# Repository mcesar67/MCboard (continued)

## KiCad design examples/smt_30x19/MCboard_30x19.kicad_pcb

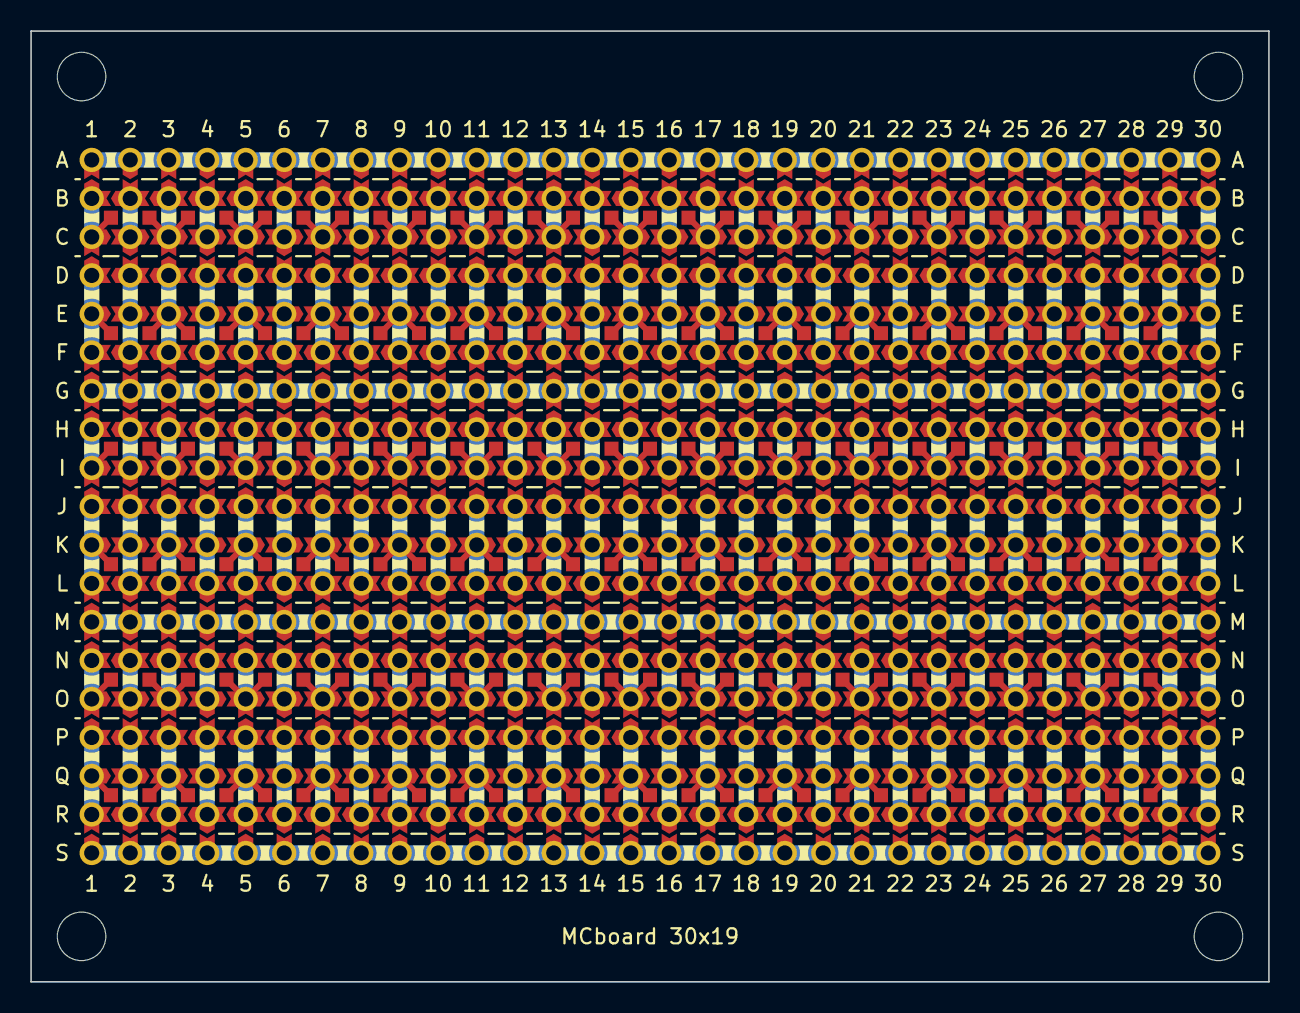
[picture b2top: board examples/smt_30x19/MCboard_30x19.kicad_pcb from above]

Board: 2 copper layers, 81.7 x 62.7 mm, 1717 parts (0 on the bottom side), 184 nets.

Parts:
PBH1, PBH2, PBH3, PBH4, PBH5, PBH6, PBH7, PBH8, PBH9, PBH10, PBH11, PBH12, PBH13, PBH14, PBH15, PBH16, PBH17, PBH18, PBH19, PBH20, PBH21, PBH22, PBH23, PBH24, PBH25, PBH26, PBH27, PBH28, PBH29, PBH30, PBH31, PBH32, PBH33, PBH34, PBH35, PBH36, PBH37, PBH38, PBH39, PBH40, PBH41, PBH42, PBH43, PBH44, PBH45, PBH46, PBH47, PBH48, PBH49, PBH50, PBH51, PBH52, PBH53, PBH54, PBH55, PBH56, PBH57, PBH58, PBH59, PBH60, PBH61, PBH62, PBH63, PBH64, PBH65, PBH66, PBH67, PBH68, PBH69, PBH70, PBH71, PBH72, PBH73, PBH74, PBH75, PBH76, PBH77, PBH78, PBH79, PBH80, PBH81, PBH82, PBH83, PBH84, PBH85, PBH86, PBH87, PBH88, PBH89, PBH90, PBH91, PBH92, PBH93, PBH94, PBH95, PBH96, PBH97, PBH98, PBH99, PBH100, PBH101, PBH102, PBH103, PBH104, PBH105, PBH106, PBH107, PBH108, PBH109, PBH110, PBH111, PBH112, PBH113, PBH114, PBH115, PBH116, PBH117, PBH118, PBH119, PBH120, PBH121, PBH122, PBH123, PBH124, PBH125, PBH126, PBH127, PBH128, PBH129, PBH130, PBH131, PBH132, PBH133, PBH134, PBH135, PBH136, PBH137, PBH138, PBH139, PBH140, PBH141, PBH142, PBH143, PBH144, PBH145, PBH146, PBH147, PBH148, PBH149, PBH150, PBH151, PBH152, PBH153, PBH154, PBH155, PBH156, PBH157, PBH158, PBH159, PBH160, PBH161, PBH162, PBH163, PBH164, PBH165, PBH166, PBH167, PBH168, PBH169, PBH170, PBH171, PBH172, PBH173, PBH174, PBH175, PBH176, PBH177, PBH178, PBH179, PBH180, PBH181, PBH182, PBH183, PBH184, PBH185, PBH186, PBH187, PBH188, PBH189, PBH190, PBH191, PBH192, PBH193, PBH194, PBH195, PBH196, PBH197, PBH198, PBH199, PBH200, PBH201, PBH202, PBH203, PBH204, PBH205, PBH206, PBH207, PBH208, PBH209, PBH210, PBH211, PBH212, PBH213, PBH214, PBH215, PBH216, PBH217, PBH218, PBH219, PBH220, PBH221, PBH222, PBH223, PBH224, PBH225, PBH226, PBH227, PBH228, PBH229, PBH230, PBH231, PBH232, PBH233, PBH234, PBH235, PBH236, PBH237, PBH238, PBH239, PBH240, PBH241, PBH242, PBH243, PBH244, PBH245, PBH246, PBH247, PBH248, PBH249, PBH250, PBH251, PBH252, PBH253, PBH254, PBH255, PBH256, PBH257, PBH258, PBH259, PBH260, PBH261, PBH262, PBH263, PBH264, PBH265, PBH266, PBH267, PBH268, PBH269, PBH270, PBH271, PBH272, PBH273, PBH274, PBH275, PBH276, PBH277, PBH278, PBH279, PBH280, PBH281, PBH282, PBH283, PBH284, PBH285, PBH286, PBH287, PBH288, PBH289, PBH290, PBH291, PBH292, PBH293, PBH294, PBH295, PBH296, PBH297, PBH298, PBH299, PBH300, PBH301, PBH302, PBH303, PBH304, PBH305, PBH306, PBH307, PBH308, PBH309, PBH310, PBH311, PBH312, PBH313, PBH314, PBH315, PBH316, PBH317, PBH318, PBH319, PBH320, PBH321, PBH322, PBH323, PBH324, PBH325, PBH326, PBH327, PBH328, PBH329, PBH330, PBH331, PBH332, PBH333, PBH334, PBH335, PBH336, PBH337, PBH338, PBH339, PBH340, PBH341, PBH342, PBH343, PBH344, PBH345, PBH346, PBH347, PBH348, PBH349, PBH350, PBH351, PBH352, PBH353, PBH354, PBH355, PBH356, PBH357, PBH358, PBH359, PBH360, PBH361, PBH362, PBH363, PBH364, PBH365, PBH366, PBH367, PBH368, PBH369, PBH370, PBH371, PBH372, PBH373, PBH374, PBH375, PBH376, PBH377, PBH378, PBH379, PBH380, PBH381, PBH382, PBH383, PBH384, PBH385, PBH386, PBH387, PBH388, PBH389, PBH390, PBH391, PBH392, PBH393, PBH394, PBH395, PBH396, PBH397, PBH398, PBH399, PBH400, PBH401, PBH402, PBH403, PBH404, PBH405, PBH406, PBH407, PBH408, PBH409, PBH410, PBH411, PBH412, PBH413, PBH414, PBH415, PBH416, PBH417, PBH418, PBH419, PBH420, PBH421, PBH422, PBH423, PBH424, PBH425, PBH426, PBH427, PBH428, PBH429, PBH430, PBH431, PBH432, PBH433, PBH434, PBH435, PBH436, PBH437, PBH438, PBH439, PBH440, PBH441, PBH442, PBH443, PBH444, PBH445, PBH446, PBH447, PBH448, PBH449, PBH450, PBH451, PBH452, PBH453, PBH454, PBH455, PBH456, PBH457, PBH458, PBH459, PBH460, PBH461, PBH462, PBH463, PBH464, PBH465, PBH466, PBH467, PBH468, PBH469, PBH470, PBH471, PBH472, PBH473, PBH474, PBH475, PBH476, PBH477, PBH478, PBH479, PBH480, PBH481, PBH482, PBH483, PBH484, PBH485, PBH486, PBH487, PBH488, PBH489, PBH490, PBH491, PBH492, PBH493, PBH494, PBH495, PBH496, PBH497, PBH498, PBH499, PBH500, PBH501, PBH502, PBH503, PBH504, PBH505, PBH506, PBH507, PBH508, PBH509, PBH510, PBH511, PBH512, PBH513, PBH514, PBH515, PBH516, PBH517, PBH518, PBH519, PBH520, PBH521, PBH522, PBH523, PBH524, PBH525, PBH526, PBH527, PBH528, PBH529, PBH530, PBH531, PBH532, PBH533, PBH534, PBH535, PBH536, PBH537, PBH538, PBH539, PBH540, PBH541, PBH542, PBH543, PBH544, PBH545, PBH546, PBH547, PBH548, PBH549, PBH550, PBH551, PBH552, PBH553, PBH554, PBH555, PBH556, PBH557, PBH558, PBH559, PBH560, PBH561, PBH562, PBH563, PBH564, PBH565, PBH566, PBH567, PBH568, PBH569, PBH570: hole; Hole
PBIS1, PBIS2, PBIS3, PBIS4, PBIS5, PBIS6, PBIS7, PBIS8, PBIS9, PBIS10, PBIS11, PBIS12, PBIS13, PBIS14, PBIS15, PBIS16, PBIS17, PBIS18, PBIS19, PBIS20, PBIS21, PBIS22, PBIS23, PBIS24, PBIS25, PBIS26, PBIS27, PBIS28, PBIS29, PBIS30, PBIS31, PBIS32, PBIS33, PBIS34, PBIS35, PBIS36, PBIS37, PBIS38, PBIS39, PBIS40, PBIS41, PBIS42, PBIS43, PBIS44, PBIS45, PBIS46, PBIS47, PBIS48, PBIS49, PBIS50, PBIS51, PBIS52, PBIS53, PBIS54, PBIS55, PBIS56, PBIS57, PBIS58, PBIS59, PBIS60, PBIS61, PBIS62, PBIS63, PBIS64, PBIS65, PBIS66, PBIS67, PBIS68, PBIS69, PBIS70, PBIS71, PBIS72, PBIS73, PBIS74, PBIS75, PBIS76, PBIS77, PBIS78, PBIS79, PBIS80, PBIS81, PBIS82, PBIS83, PBIS84, PBIS85, PBIS86, PBIS87, PBIS88, PBIS89, PBIS90, PBIS91, PBIS92, PBIS93, PBIS94, PBIS95, PBIS96, PBIS97, PBIS98, PBIS99, PBIS100, PBIS101, PBIS102, PBIS103, PBIS104, PBIS105, PBIS106, PBIS107, PBIS108, PBIS109, PBIS110, PBIS111, PBIS112, PBIS113, PBIS114, PBIS115, PBIS116, PBIS117, PBIS118, PBIS119, PBIS120, PBIS121, PBIS122, PBIS123, PBIS124, PBIS125, PBIS126, PBIS127, PBIS128, PBIS129, PBIS130, PBIS131, PBIS132, PBIS133, PBIS134, PBIS135, PBIS136, PBIS137, PBIS138, PBIS139, PBIS140, PBIS141, PBIS142, PBIS143, PBIS144, PBIS145, PBIS146, PBIS147, PBIS148, PBIS149, PBIS150, PBIS151, PBIS152, PBIS153, PBIS154, PBIS155, PBIS156, PBIS157, PBIS158, PBIS159, PBIS160, PBIS161, PBIS162, PBIS163, PBIS164, PBIS165, PBIS166, PBIS167, PBIS168: island; Island
PBJP1, PBJP2, PBJP3, PBJP4, PBJP5, PBJP6, PBJP7, PBJP8, PBJP9, PBJP10, PBJP11, PBJP12, PBJP13, PBJP14, PBJP15, PBJP16, PBJP17, PBJP18, PBJP19, PBJP20, PBJP21, PBJP22, PBJP23, PBJP24, PBJP25, PBJP26, PBJP27, PBJP28, PBJP29, PBJP30, PBJP31, PBJP32, PBJP33, PBJP34, PBJP35, PBJP36, PBJP37, PBJP38, PBJP39, PBJP40, PBJP41, PBJP42, PBJP43, PBJP44, PBJP45, PBJP46, PBJP47, PBJP48, PBJP49, PBJP50, PBJP51, PBJP52, PBJP53, PBJP54, PBJP55, PBJP56, PBJP57, PBJP58, PBJP59, PBJP60, PBJP61, PBJP62, PBJP63, PBJP64, PBJP65, PBJP66, PBJP67, PBJP68, PBJP69, PBJP70, PBJP71, PBJP72, PBJP73, PBJP74, PBJP75, PBJP76, PBJP77, PBJP78, PBJP79, PBJP80, PBJP81, PBJP82, PBJP83, PBJP84, PBJP85, PBJP86, PBJP87, PBJP88, PBJP89, PBJP90, PBJP91, PBJP92, PBJP93, PBJP94, PBJP95, PBJP96, PBJP97, PBJP98, PBJP99, PBJP100, PBJP101, PBJP102, PBJP103, PBJP104, PBJP105, PBJP106, PBJP107, PBJP108, PBJP109, PBJP110, PBJP111, PBJP112, PBJP113, PBJP114, PBJP115, PBJP116, PBJP117, PBJP118, PBJP119, PBJP120, PBJP121, PBJP122, PBJP123, PBJP124, PBJP125, PBJP126, PBJP127, PBJP128, PBJP129, PBJP130, PBJP131, PBJP132, PBJP133, PBJP134, PBJP135, PBJP136, PBJP137, PBJP138, PBJP139, PBJP140, PBJP141, PBJP142, PBJP143, PBJP144, PBJP145, PBJP146, PBJP147, PBJP148, PBJP149, PBJP150, PBJP151, PBJP152, PBJP153, PBJP154, PBJP155, PBJP156, PBJP157, PBJP158, PBJP159, PBJP160, PBJP161, PBJP162, PBJP163, PBJP164, PBJP165, PBJP166, PBJP167, PBJP168, PBJP169, PBJP170, PBJP171, PBJP172, PBJP173, PBJP174, PBJP175, PBJP176, PBJP177, PBJP178, PBJP179, PBJP180, PBJP181, PBJP182, PBJP183, PBJP184, PBJP185, PBJP186, PBJP187, PBJP188, PBJP189, PBJP190, PBJP191, PBJP192, PBJP193, PBJP194, PBJP195, PBJP196, PBJP197, PBJP198, PBJP199, PBJP200, PBJP201, PBJP202, PBJP203, PBJP204, PBJP205, PBJP206, PBJP207, PBJP208, PBJP209, PBJP210, PBJP211, PBJP212, PBJP213, PBJP214, PBJP215, PBJP216, PBJP217, PBJP218, PBJP219, PBJP220, PBJP221, PBJP222, PBJP223, PBJP224, PBJP225, PBJP226, PBJP227, PBJP228, PBJP229, PBJP230, PBJP231, PBJP232, PBJP233, PBJP234, PBJP235, PBJP236, PBJP237, PBJP238, PBJP239, PBJP240, PBJP241, PBJP242, PBJP243, PBJP244, PBJP245, PBJP246, PBJP247, PBJP248, PBJP249, PBJP250, PBJP251, PBJP252, PBJP253, PBJP254, PBJP255, PBJP256, PBJP257, PBJP258, PBJP259, PBJP260, PBJP261, PBJP262, PBJP263, PBJP264, PBJP265, PBJP266, PBJP267, PBJP268, PBJP269, PBJP270: chevron; ChevronJumper
PBJT1, PBJT2, PBJT3, PBJT4, PBJT5, PBJT6, PBJT7, PBJT8, PBJT9, PBJT10, PBJT11, PBJT12, PBJT13, PBJT14, PBJT15, PBJT16, PBJT17, PBJT18, PBJT19, PBJT20, PBJT21, PBJT22, PBJT23, PBJT24, PBJT25, PBJT26, PBJT27, PBJT28, PBJT29, PBJT30, PBJT31, PBJT32, PBJT33, PBJT34, PBJT35, PBJT36, PBJT37, PBJT38, PBJT39, PBJT40, PBJT41, PBJT42, PBJT43, PBJT44, PBJT45, PBJT46, PBJT47, PBJT48, PBJT49, PBJT50, PBJT51, PBJT52, PBJT53, PBJT54, PBJT55, PBJT56, PBJT57, PBJT58, PBJT59, PBJT60, PBJT61, PBJT62, PBJT63, PBJT64, PBJT65, PBJT66, PBJT67, PBJT68, PBJT69, PBJT70, PBJT71, PBJT72, PBJT73, PBJT74, PBJT75, PBJT76, PBJT77, PBJT78, PBJT79, PBJT80, PBJT81, PBJT82, PBJT83, PBJT84, PBJT85, PBJT86, PBJT87, PBJT88, PBJT89, PBJT90, PBJT91, PBJT92, PBJT93, PBJT94, PBJT95, PBJT96, PBJT97, PBJT98, PBJT99, PBJT100, PBJT101, PBJT102, PBJT103, PBJT104, PBJT105, PBJT106, PBJT107, PBJT108, PBJT109, PBJT110, PBJT111, PBJT112, PBJT113, PBJT114, PBJT115, PBJT116, PBJT117, PBJT118, PBJT119, PBJT120, PBJT121, PBJT122, PBJT123, PBJT124, PBJT125, PBJT126, PBJT127, PBJT128, PBJT129, PBJT130, PBJT131, PBJT132, PBJT133, PBJT134, PBJT135, PBJT136, PBJT137, PBJT138, PBJT139, PBJT140, PBJT141, PBJT142, PBJT143, PBJT144, PBJT145, PBJT146, PBJT147, PBJT148, PBJT149, PBJT150, PBJT151, PBJT152, PBJT153, PBJT154, PBJT155, PBJT156, PBJT157, PBJT158, PBJT159, PBJT160, PBJT161, PBJT162, PBJT163, PBJT164, PBJT165, PBJT166, PBJT167, PBJT168, PBJT169, PBJT170, PBJT171, PBJT172, PBJT173, PBJT174, PBJT175, PBJT176, PBJT177, PBJT178, PBJT179, PBJT180, PBJT181, PBJT182, PBJT183, PBJT184, PBJT185, PBJT186, PBJT187, PBJT188, PBJT189, PBJT190, PBJT191, PBJT192, PBJT193, PBJT194, PBJT195, PBJT196, PBJT197, PBJT198, PBJT199, PBJT200, PBJT201, PBJT202, PBJT203, PBJT204, PBJT205, PBJT206, PBJT207, PBJT208, PBJT209, PBJT210, PBJT211, PBJT212, PBJT213, PBJT214, PBJT215, PBJT216, PBJT217, PBJT218, PBJT219, PBJT220, PBJT221, PBJT222, PBJT223, PBJT224, PBJT225, PBJT226, PBJT227, PBJT228, PBJT229, PBJT230, PBJT231, PBJT232, PBJT233, PBJT234, PBJT235, PBJT236, PBJT237, PBJT238, PBJT239, PBJT240, PBJT241, PBJT242, PBJT243, PBJT244, PBJT245, PBJT246, PBJT247, PBJT248, PBJT249, PBJT250, PBJT251, PBJT252, PBJT253, PBJT254, PBJT255, PBJT256, PBJT257, PBJT258, PBJT259, PBJT260, PBJT261, PBJT262, PBJT263, PBJT264, PBJT265, PBJT266, PBJT267, PBJT268, PBJT269, PBJT270, PBJT271, PBJT272, PBJT273, PBJT274, PBJT275, PBJT276, PBJT277, PBJT278, PBJT279, PBJT280, PBJT281, PBJT282, PBJT283, PBJT284, PBJT285, PBJT286, PBJT287, PBJT288, PBJT289, PBJT290, PBJT291, PBJT292, PBJT293, PBJT294, PBJT295, PBJT296, PBJT297, PBJT298, PBJT299, PBJT300, PBJT301, PBJT302, PBJT303, PBJT304, PBJT305, PBJT306, PBJT307, PBJT308, PBJT309, PBJT310, PBJT311, PBJT312, PBJT313, PBJT314, PBJT315, PBJT316, PBJT317, PBJT318, PBJT319, PBJT320, PBJT321, PBJT322, PBJT323, PBJT324, PBJT325, PBJT326, PBJT327, PBJT328, PBJT329, PBJT330, PBJT331, PBJT332, PBJT333, PBJT334, PBJT335, PBJT336, PBJT337, PBJT338, PBJT339, PBJT340, PBJT341, PBJT342, PBJT343, PBJT344, PBJT345, PBJT346, PBJT347, PBJT348, PBJT349, PBJT350, PBJT351, PBJT352, PBJT353, PBJT354, PBJT355, PBJT356, PBJT357, PBJT358, PBJT359, PBJT360, PBJT361, PBJT362, PBJT363, PBJT364, PBJT365, PBJT366, PBJT367, PBJT368, PBJT369, PBJT370, PBJT371, PBJT372, PBJT373, PBJT374, PBJT375, PBJT376, PBJT377, PBJT378, PBJT379, PBJT380, PBJT381, PBJT382, PBJT383, PBJT384, PBJT385, PBJT386, PBJT387, PBJT388, PBJT389, PBJT390, PBJT391, PBJT392, PBJT393, PBJT394, PBJT395, PBJT396, PBJT397, PBJT398, PBJT399, PBJT400, PBJT401, PBJT402, PBJT403, PBJT404, PBJT405, PBJT406, PBJT407, PBJT408, PBJT409, PBJT410, PBJT411, PBJT412, PBJT413, PBJT414, PBJT415, PBJT416, PBJT417, PBJT418, PBJT419, PBJT420, PBJT421, PBJT422, PBJT423, PBJT424, PBJT425, PBJT426, PBJT427, PBJT428, PBJT429, PBJT430, PBJT431, PBJT432, PBJT433, PBJT434, PBJT435, PBJT436, PBJT437, PBJT438, PBJT439, PBJT440, PBJT441, PBJT442, PBJT443, PBJT444, PBJT445, PBJT446, PBJT447, PBJT448, PBJT449, PBJT450, PBJT451, PBJT452, PBJT453, PBJT454, PBJT455, PBJT456, PBJT457, PBJT458, PBJT459, PBJT460, PBJT461, PBJT462, PBJT463, PBJT464, PBJT465, PBJT466, PBJT467, PBJT468, PBJT469, PBJT470, PBJT471, PBJT472, PBJT473, PBJT474, PBJT475, PBJT476, PBJT477, PBJT478, PBJT479, PBJT480, PBJT481, PBJT482, PBJT483, PBJT484, PBJT485, PBJT486, PBJT487, PBJT488, PBJT489, PBJT490, PBJT491, PBJT492, PBJT493, PBJT494, PBJT495, PBJT496, PBJT497, PBJT498, PBJT499, PBJT500, PBJT501, PBJT502, PBJT503, PBJT504, PBJT505, PBJT506, PBJT507, PBJT508, PBJT509, PBJT510, PBJT511, PBJT512, PBJT513, PBJT514, PBJT515, PBJT516, PBJT517, PBJT518, PBJT519, PBJT520, PBJT521, PBJT522, PBJT523, PBJT524, PBJT525, PBJT526, PBJT527, PBJT528, PBJT529, PBJT530, PBJT531, PBJT532, PBJT533, PBJT534, PBJT535, PBJT536, PBJT537, PBJT538, PBJT539, PBJT540, PBJT541, PBJT542, PBJT543, PBJT544, PBJT545, PBJT546, PBJT547, PBJT548, PBJT549, PBJT550, PBJT551, PBJT552, PBJT553, PBJT554, PBJT555, PBJT556, PBJT557, PBJT558, PBJT559, PBJT560, PBJT561, PBJT562, PBJT563, PBJT564, PBJT565, PBJT566, PBJT567, PBJT568, PBJT569, PBJT570, PBJT571, PBJT572, PBJT573, PBJT574, PBJT575, PBJT576, PBJT577, PBJT578, PBJT579, PBJT580, PBJT581, PBJT582, PBJT583, PBJT584, PBJT585, PBJT586, PBJT587, PBJT588, PBJT589, PBJT590, PBJT591, PBJT592, PBJT593, PBJT594, PBJT595, PBJT596, PBJT597, PBJT598, PBJT599, PBJT600, PBJT601, PBJT602, PBJT603, PBJT604, PBJT605, PBJT606, PBJT607, PBJT608, PBJT609, PBJT610, PBJT611, PBJT612, PBJT613, PBJT614, PBJT615, PBJT616, PBJT617, PBJT618, PBJT619, PBJT620, PBJT621, PBJT622, PBJT623, PBJT624, PBJT625, PBJT626, PBJT627, PBJT628, PBJT629, PBJT630, PBJT631, PBJT632, PBJT633, PBJT634, PBJT635, PBJT636, PBJT637, PBJT638, PBJT639, PBJT640, PBJT641, PBJT642, PBJT643, PBJT644, PBJT645, PBJT646, PBJT647, PBJT648, PBJT649, PBJT650, PBJT651, PBJT652, PBJT653, PBJT654, PBJT655, PBJT656, PBJT657, PBJT658, PBJT659, PBJT660, PBJT661, PBJT662, PBJT663, PBJT664, PBJT665, PBJT666, PBJT667, PBJT668, PBJT669, PBJT670, PBJT671, PBJT672, PBJT673, PBJT674, PBJT675, PBJT676, PBJT677, PBJT678, PBJT679, PBJT680, PBJT681, PBJT682, PBJT683, PBJT684, PBJT685, PBJT686, PBJT687, PBJT688, PBJT689, PBJT690, PBJT691, PBJT692, PBJT693, PBJT694, PBJT695, PBJT696, PBJT697, PBJT698, PBJT699, PBJT700, PBJT701, PBJT702, PBJT703, PBJT704, PBJT705: chevron; ChevronJumper
PBMH1, PBMH2, PBMH3, PBMH4: mounting hole; MountingHole

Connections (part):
BUS_R1: PBH1.1, PBH20.1, PBH39.1, PBH58.1, PBH77.1, PBH96.1, PBH115.1, PBH134.1, PBH153.1, PBH172.1, PBH191.1, PBH210.1, PBH229.1, PBH248.1, PBH267.1, PBH286.1, PBH305.1, PBH324.1, PBH343.1, PBH362.1, PBH381.1, PBH400.1, PBH419.1, PBH438.1, PBH457.1, PBH476.1, PBH495.1, PBH514.1, PBH533.1, PBH552.1, PBJP1.1, PBJP10.1, PBJP19.1, PBJP28.1, PBJP37.1, PBJP46.1, PBJP55.1, PBJP64.1, PBJP73.1, PBJP82.1, PBJP91.1, PBJP100.1, PBJP109.1, PBJP118.1, PBJP127.1, PBJP136.1, PBJP145.1, PBJP154.1, PBJP163.1, PBJP172.1, PBJP181.1, PBJP190.1, PBJP199.1, PBJP208.1, PBJP217.1, PBJP226.1, PBJP235.1, PBJP244.1, PBJP253.1, PBJP262.1, PBJT436.2, PBJT445.1, PBJT454.2, PBJT463.1, PBJT472.2, PBJT481.1, PBJT490.2, PBJT499.1, PBJT508.2, PBJT517.1, PBJT526.2, PBJT535.1, PBJT544.2, PBJT553.1, PBJT562.2, PBJT571.1, PBJT580.2, PBJT589.1, PBJT598.2, PBJT607.1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
BUS_R7: PBH7.1, PBH26.1, PBH45.1, PBH64.1, PBH83.1, PBH102.1, PBH121.1, PBH140.1, PBH159.1, PBH178.1, PBH197.1, PBH216.1, PBH235.1, PBH254.1, PBH273.1, PBH292.1, PBH311.1, PBH330.1, PBH349.1, PBH368.1, PBH387.1, PBH406.1, PBH425.1, PBH444.1, PBH463.1, PBH482.1, PBH501.1, PBH520.1, PBH539.1, PBH558.1, PBJP3.2, PBJP4.1, PBJP12.2, PBJP13.1, PBJP21.2, PBJP22.1, PBJP30.2, PBJP31.1, PBJP39.2, PBJP40.1, PBJP48.2, PBJP49.1, PBJP57.2, PBJP58.1, PBJP66.2, PBJP67.1, PBJP75.2, PBJP76.1, PBJP84.2, PBJP85.1, PBJP93.2, PBJP94.1, PBJP102.2, PBJP103.1, PBJP111.2, PBJP112.1, PBJP120.2, PBJP121.1, PBJP129.2, PBJP130.1, PBJP138.2, PBJP139.1, PBJP147.2, PBJP148.1, PBJP156.2, PBJP157.1, PBJP165.2, PBJP166.1, PBJP174.2, PBJP175.1, PBJP183.2, PBJP184.1, PBJP192.2, PBJP193.1, PBJP201.2, PBJP202.1, PBJP210.2, PBJP211.1, PBJP219.2, PBJP220.1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
BUS_R13: PBH13.1, PBH32.1, PBH51.1, PBH70.1, PBH89.1, PBH108.1, PBH127.1, PBH146.1, PBH165.1, PBH184.1, PBH203.1, PBH222.1, PBH241.1, PBH260.1, PBH279.1, PBH298.1, PBH317.1, PBH336.1, PBH355.1, PBH374.1, PBH393.1, PBH412.1, PBH431.1, PBH450.1, PBH469.1, PBH488.1, PBH507.1, PBH526.1, PBH545.1, PBH564.1, PBJP6.2, PBJP7.1, PBJP15.2, PBJP16.1, PBJP24.2, PBJP25.1, PBJP33.2, PBJP34.1, PBJP42.2, PBJP43.1, PBJP51.2, PBJP52.1, PBJP60.2, PBJP61.1, PBJP69.2, PBJP70.1, PBJP78.2, PBJP79.1, PBJP87.2, PBJP88.1, PBJP96.2, PBJP97.1, PBJP105.2, PBJP106.1, PBJP114.2, PBJP115.1, PBJP123.2, PBJP124.1, PBJP132.2, PBJP133.1, PBJP141.2, PBJP142.1, PBJP150.2, PBJP151.1, PBJP159.2, PBJP160.1, PBJP168.2, PBJP169.1, PBJP177.2, PBJP178.1, PBJP186.2, PBJP187.1, PBJP195.2, PBJP196.1, PBJP204.2, PBJP205.1, PBJP213.2, PBJP214.1, PBJP222.2, PBJP223.1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
BUS_R19: PBH19.1, PBH38.1, PBH57.1, PBH76.1, PBH95.1, PBH114.1, PBH133.1, PBH152.1, PBH171.1, PBH190.1, PBH209.1, PBH228.1, PBH247.1, PBH266.1, PBH285.1, PBH304.1, PBH323.1, PBH342.1, PBH361.1, PBH380.1, PBH399.1, PBH418.1, PBH437.1, PBH456.1, PBH475.1, PBH494.1, PBH513.1, PBH532.1, PBH551.1, PBH570.1, PBJP9.2, PBJP18.2, PBJP27.2, PBJP36.2, PBJP45.2, PBJP54.2, PBJP63.2, PBJP72.2, PBJP81.2, PBJP90.2, PBJP99.2, PBJP108.2, PBJP117.2, PBJP126.2, PBJP135.2, PBJP144.2, PBJP153.2, PBJP162.2, PBJP171.2, PBJP180.2, PBJP189.2, PBJP198.2, PBJP207.2, PBJP216.2, PBJP225.2, PBJP234.2, PBJP243.2, PBJP252.2, PBJP261.2, PBJP270.2, PBJT444.1, PBJT453.2, PBJT462.1, PBJT471.2, PBJT480.1, PBJT489.2, PBJT498.1, PBJT507.2, PBJT516.1, PBJT525.2, PBJT534.1, PBJT543.2, PBJT552.1, PBJT561.2, PBJT570.1, PBJT579.2, PBJT588.1, PBJT597.2, PBJT606.1, PBJT615.2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
C1_R2: PBH2.1, PBH3.1, PBIS1.1, PBJP1.2, PBJP2.1, PBJT1.2, PBJT30.1, PBJT436.1, PBJT437.2
C1_R4: PBH4.1, PBH5.1, PBH6.1, PBIS29.1, PBJP2.2, PBJP3.1, PBJT59.2, PBJT88.1, PBJT117.2, PBJT437.1, PBJT438.2
C1_R8: PBH8.1, PBH9.1, PBIS57.1, PBJP4.2, PBJP5.1, PBJT146.2, PBJT175.1, PBJT439.1, PBJT440.2
C1_R10: PBH10.1, PBH11.1, PBH12.1, PBIS85.1, PBJP5.2, PBJP6.1, PBJT204.2, PBJT233.1, PBJT262.2, PBJT440.1, PBJT441.2
C1_R14: PBH14.1, PBH15.1, PBIS113.1, PBJP7.2, PBJP8.1, PBJT291.2, PBJT320.1, PBJT442.1, PBJT443.2
C1_R16: PBH16.1, PBH17.1, PBH18.1, PBIS141.1, PBJP8.2, PBJP9.1, PBJT349.2, PBJT378.1, PBJT407.2, PBJT443.1, PBJT444.2
C2_R2: PBH21.1, PBH22.1, PBJP10.2, PBJP11.1, PBJT1.1, PBJT2.2, PBJT30.2, PBJT31.1, PBJT445.2, PBJT446.1
C2_R4: PBH23.1, PBH24.1, PBH25.1, PBJP11.2, PBJP12.1, PBJT59.1, PBJT60.2, PBJT88.2, PBJT89.1, PBJT117.1, PBJT118.2, PBJT446.2, PBJT447.1
C2_R8: PBH27.1, PBH28.1, PBJP13.2, PBJP14.1, PBJT146.1, PBJT147.2, PBJT175.2, PBJT176.1, PBJT448.2, PBJT449.1
C2_R10: PBH29.1, PBH30.1, PBH31.1, PBJP14.2, PBJP15.1, PBJT204.1, PBJT205.2, PBJT233.2, PBJT234.1, PBJT262.1, PBJT263.2, PBJT449.2, PBJT450.1
C2_R14: PBH33.1, PBH34.1, PBJP16.2, PBJP17.1, PBJT291.1, PBJT292.2, PBJT320.2, PBJT321.1, PBJT451.2, PBJT452.1
C2_R16: PBH35.1, PBH36.1, PBH37.1, PBJP17.2, PBJP18.1, PBJT349.1, PBJT350.2, PBJT378.2, PBJT379.1, PBJT407.1, PBJT408.2, PBJT452.2, PBJT453.1
C3_R2: PBH40.1, PBH41.1, PBIS2.1, PBIS3.1, PBJP19.2, PBJP20.1, PBJT2.1, PBJT3.2, PBJT31.2, PBJT32.1, PBJT454.1, PBJT455.2
C3_R4: PBH42.1, PBH43.1, PBH44.1, PBIS30.1, PBIS31.1, PBJP20.2, PBJP21.1, PBJT60.1, PBJT61.2, PBJT89.2, PBJT90.1, PBJT118.1, PBJT119.2, PBJT455.1, PBJT456.2
C3_R8: PBH46.1, PBH47.1, PBIS58.1, PBIS59.1, PBJP22.2, PBJP23.1, PBJT147.1, PBJT148.2, PBJT176.2, PBJT177.1, PBJT457.1, PBJT458.2
C3_R10: PBH48.1, PBH49.1, PBH50.1, PBIS86.1, PBIS87.1, PBJP23.2, PBJP24.1, PBJT205.1, PBJT206.2, PBJT234.2, PBJT235.1, PBJT263.1, PBJT264.2, PBJT458.1, PBJT459.2
C3_R14: PBH52.1, PBH53.1, PBIS114.1, PBIS115.1, PBJP25.2, PBJP26.1, PBJT292.1, PBJT293.2, PBJT321.2, PBJT322.1, PBJT460.1, PBJT461.2
C3_R16: PBH54.1, PBH55.1, PBH56.1, PBIS142.1, PBIS143.1, PBJP26.2, PBJP27.1, PBJT350.1, PBJT351.2, PBJT379.2, PBJT380.1, PBJT408.1, PBJT409.2, PBJT461.1, PBJT462.2
C4_R2: PBH59.1, PBH60.1, PBJP28.2, PBJP29.1, PBJT3.1, PBJT4.2, PBJT32.2, PBJT33.1, PBJT463.2, PBJT464.1
C4_R4: PBH61.1, PBH62.1, PBH63.1, PBJP29.2, PBJP30.1, PBJT61.1, PBJT62.2, PBJT90.2, PBJT91.1, PBJT119.1, PBJT120.2, PBJT464.2, PBJT465.1
C4_R8: PBH65.1, PBH66.1, PBJP31.2, PBJP32.1, PBJT148.1, PBJT149.2, PBJT177.2, PBJT178.1, PBJT466.2, PBJT467.1
C4_R10: PBH67.1, PBH68.1, PBH69.1, PBJP32.2, PBJP33.1, PBJT206.1, PBJT207.2, PBJT235.2, PBJT236.1, PBJT264.1, PBJT265.2, PBJT467.2, PBJT468.1
C4_R14: PBH71.1, PBH72.1, PBJP34.2, PBJP35.1, PBJT293.1, PBJT294.2, PBJT322.2, PBJT323.1, PBJT469.2, PBJT470.1
C4_R16: PBH73.1, PBH74.1, PBH75.1, PBJP35.2, PBJP36.1, PBJT351.1, PBJT352.2, PBJT380.2, PBJT381.1, PBJT409.1, PBJT410.2, PBJT470.2, PBJT471.1
C5_R2: PBH78.1, PBH79.1, PBIS4.1, PBIS5.1, PBJP37.2, PBJP38.1, PBJT4.1, PBJT5.2, PBJT33.2, PBJT34.1, PBJT472.1, PBJT473.2
C5_R4: PBH80.1, PBH81.1, PBH82.1, PBIS32.1, PBIS33.1, PBJP38.2, PBJP39.1, PBJT62.1, PBJT63.2, PBJT91.2, PBJT92.1, PBJT120.1, PBJT121.2, PBJT473.1, PBJT474.2
C5_R8: PBH84.1, PBH85.1, PBIS60.1, PBIS61.1, PBJP40.2, PBJP41.1, PBJT149.1, PBJT150.2, PBJT178.2, PBJT179.1, PBJT475.1, PBJT476.2
C5_R10: PBH86.1, PBH87.1, PBH88.1, PBIS88.1, PBIS89.1, PBJP41.2, PBJP42.1, PBJT207.1, PBJT208.2, PBJT236.2, PBJT237.1, PBJT265.1, PBJT266.2, PBJT476.1, PBJT477.2
C5_R14: PBH90.1, PBH91.1, PBIS116.1, PBIS117.1, PBJP43.2, PBJP44.1, PBJT294.1, PBJT295.2, PBJT323.2, PBJT324.1, PBJT478.1, PBJT479.2
C5_R16: PBH92.1, PBH93.1, PBH94.1, PBIS144.1, PBIS145.1, PBJP44.2, PBJP45.1, PBJT352.1, PBJT353.2, PBJT381.2, PBJT382.1, PBJT410.1, PBJT411.2, PBJT479.1, PBJT480.2
C6_R2: PBH97.1, PBH98.1, PBJP46.2, PBJP47.1, PBJT5.1, PBJT6.2, PBJT34.2, PBJT35.1, PBJT481.2, PBJT482.1
C6_R4: PBH99.1, PBH100.1, PBH101.1, PBJP47.2, PBJP48.1, PBJT63.1, PBJT64.2, PBJT92.2, PBJT93.1, PBJT121.1, PBJT122.2, PBJT482.2, PBJT483.1
C6_R8: PBH103.1, PBH104.1, PBJP49.2, PBJP50.1, PBJT150.1, PBJT151.2, PBJT179.2, PBJT180.1, PBJT484.2, PBJT485.1
C6_R10: PBH105.1, PBH106.1, PBH107.1, PBJP50.2, PBJP51.1, PBJT208.1, PBJT209.2, PBJT237.2, PBJT238.1, PBJT266.1, PBJT267.2, PBJT485.2, PBJT486.1
C6_R14: PBH109.1, PBH110.1, PBJP52.2, PBJP53.1, PBJT295.1, PBJT296.2, PBJT324.2, PBJT325.1, PBJT487.2, PBJT488.1
C6_R16: PBH111.1, PBH112.1, PBH113.1, PBJP53.2, PBJP54.1, PBJT353.1, PBJT354.2, PBJT382.2, PBJT383.1, PBJT411.1, PBJT412.2, PBJT488.2, PBJT489.1
C7_R2: PBH116.1, PBH117.1, PBIS6.1, PBIS7.1, PBJP55.2, PBJP56.1, PBJT6.1, PBJT7.2, PBJT35.2, PBJT36.1, PBJT490.1, PBJT491.2
C7_R4: PBH118.1, PBH119.1, PBH120.1, PBIS34.1, PBIS35.1, PBJP56.2, PBJP57.1, PBJT64.1, PBJT65.2, PBJT93.2, PBJT94.1, PBJT122.1, PBJT123.2, PBJT491.1, PBJT492.2
C7_R8: PBH122.1, PBH123.1, PBIS62.1, PBIS63.1, PBJP58.2, PBJP59.1, PBJT151.1, PBJT152.2, PBJT180.2, PBJT181.1, PBJT493.1, PBJT494.2
C7_R10: PBH124.1, PBH125.1, PBH126.1, PBIS90.1, PBIS91.1, PBJP59.2, PBJP60.1, PBJT209.1, PBJT210.2, PBJT238.2, PBJT239.1, PBJT267.1, PBJT268.2, PBJT494.1, PBJT495.2
C7_R14: PBH128.1, PBH129.1, PBIS118.1, PBIS119.1, PBJP61.2, PBJP62.1, PBJT296.1, PBJT297.2, PBJT325.2, PBJT326.1, PBJT496.1, PBJT497.2
C7_R16: PBH130.1, PBH131.1, PBH132.1, PBIS146.1, PBIS147.1, PBJP62.2, PBJP63.1, PBJT354.1, PBJT355.2, PBJT383.2, PBJT384.1, PBJT412.1, PBJT413.2, PBJT497.1, PBJT498.2
C8_R2: PBH135.1, PBH136.1, PBJP64.2, PBJP65.1, PBJT7.1, PBJT8.2, PBJT36.2, PBJT37.1, PBJT499.2, PBJT500.1
C8_R4: PBH137.1, PBH138.1, PBH139.1, PBJP65.2, PBJP66.1, PBJT65.1, PBJT66.2, PBJT94.2, PBJT95.1, PBJT123.1, PBJT124.2, PBJT500.2, PBJT501.1
C8_R8: PBH141.1, PBH142.1, PBJP67.2, PBJP68.1, PBJT152.1, PBJT153.2, PBJT181.2, PBJT182.1, PBJT502.2, PBJT503.1
C8_R10: PBH143.1, PBH144.1, PBH145.1, PBJP68.2, PBJP69.1, PBJT210.1, PBJT211.2, PBJT239.2, PBJT240.1, PBJT268.1, PBJT269.2, PBJT503.2, PBJT504.1
C8_R14: PBH147.1, PBH148.1, PBJP70.2, PBJP71.1, PBJT297.1, PBJT298.2, PBJT326.2, PBJT327.1, PBJT505.2, PBJT506.1
C8_R16: PBH149.1, PBH150.1, PBH151.1, PBJP71.2, PBJP72.1, PBJT355.1, PBJT356.2, PBJT384.2, PBJT385.1, PBJT413.1, PBJT414.2, PBJT506.2, PBJT507.1
C9_R2: PBH154.1, PBH155.1, PBIS8.1, PBIS9.1, PBJP73.2, PBJP74.1, PBJT8.1, PBJT9.2, PBJT37.2, PBJT38.1, PBJT508.1, PBJT509.2
C9_R4: PBH156.1, PBH157.1, PBH158.1, PBIS36.1, PBIS37.1, PBJP74.2, PBJP75.1, PBJT66.1, PBJT67.2, PBJT95.2, PBJT96.1, PBJT124.1, PBJT125.2, PBJT509.1, PBJT510.2
C9_R8: PBH160.1, PBH161.1, PBIS64.1, PBIS65.1, PBJP76.2, PBJP77.1, PBJT153.1, PBJT154.2, PBJT182.2, PBJT183.1, PBJT511.1, PBJT512.2
C9_R10: PBH162.1, PBH163.1, PBH164.1, PBIS92.1, PBIS93.1, PBJP77.2, PBJP78.1, PBJT211.1, PBJT212.2, PBJT240.2, PBJT241.1, PBJT269.1, PBJT270.2, PBJT512.1, PBJT513.2
C9_R14: PBH166.1, PBH167.1, PBIS120.1, PBIS121.1, PBJP79.2, PBJP80.1, PBJT298.1, PBJT299.2, PBJT327.2, PBJT328.1, PBJT514.1, PBJT515.2
C9_R16: PBH168.1, PBH169.1, PBH170.1, PBIS148.1, PBIS149.1, PBJP80.2, PBJP81.1, PBJT356.1, PBJT357.2, PBJT385.2, PBJT386.1, PBJT414.1, PBJT415.2, PBJT515.1, PBJT516.2
C10_R2: PBH173.1, PBH174.1, PBJP82.2, PBJP83.1, PBJT9.1, PBJT10.2, PBJT38.2, PBJT39.1, PBJT517.2, PBJT518.1
C10_R4: PBH175.1, PBH176.1, PBH177.1, PBJP83.2, PBJP84.1, PBJT67.1, PBJT68.2, PBJT96.2, PBJT97.1, PBJT125.1, PBJT126.2, PBJT518.2, PBJT519.1
C10_R8: PBH179.1, PBH180.1, PBJP85.2, PBJP86.1, PBJT154.1, PBJT155.2, PBJT183.2, PBJT184.1, PBJT520.2, PBJT521.1
C10_R10: PBH181.1, PBH182.1, PBH183.1, PBJP86.2, PBJP87.1, PBJT212.1, PBJT213.2, PBJT241.2, PBJT242.1, PBJT270.1, PBJT271.2, PBJT521.2, PBJT522.1
C10_R14: PBH185.1, PBH186.1, PBJP88.2, PBJP89.1, PBJT299.1, PBJT300.2, PBJT328.2, PBJT329.1, PBJT523.2, PBJT524.1
C10_R16: PBH187.1, PBH188.1, PBH189.1, PBJP89.2, PBJP90.1, PBJT357.1, PBJT358.2, PBJT386.2, PBJT387.1, PBJT415.1, PBJT416.2, PBJT524.2, PBJT525.1
C11_R2: PBH192.1, PBH193.1, PBIS10.1, PBIS11.1, PBJP91.2, PBJP92.1, PBJT10.1, PBJT11.2, PBJT39.2, PBJT40.1, PBJT526.1, PBJT527.2
C11_R4: PBH194.1, PBH195.1, PBH196.1, PBIS38.1, PBIS39.1, PBJP92.2, PBJP93.1, PBJT68.1, PBJT69.2, PBJT97.2, PBJT98.1, PBJT126.1, PBJT127.2, PBJT527.1, PBJT528.2
C11_R8: PBH198.1, PBH199.1, PBIS66.1, PBIS67.1, PBJP94.2, PBJP95.1, PBJT155.1, PBJT156.2, PBJT184.2, PBJT185.1, PBJT529.1, PBJT530.2
C11_R10: PBH200.1, PBH201.1, PBH202.1, PBIS94.1, PBIS95.1, PBJP95.2, PBJP96.1, PBJT213.1, PBJT214.2, PBJT242.2, PBJT243.1, PBJT271.1, PBJT272.2, PBJT530.1, PBJT531.2
C11_R14: PBH204.1, PBH205.1, PBIS122.1, PBIS123.1, PBJP97.2, PBJP98.1, PBJT300.1, PBJT301.2, PBJT329.2, PBJT330.1, PBJT532.1, PBJT533.2
C11_R16: PBH206.1, PBH207.1, PBH208.1, PBIS150.1, PBIS151.1, PBJP98.2, PBJP99.1, PBJT358.1, PBJT359.2, PBJT387.2, PBJT388.1, PBJT416.1, PBJT417.2, PBJT533.1, PBJT534.2
C12_R2: PBH211.1, PBH212.1, PBJP100.2, PBJP101.1, PBJT11.1, PBJT12.2, PBJT40.2, PBJT41.1, PBJT535.2, PBJT536.1
C12_R4: PBH213.1, PBH214.1, PBH215.1, PBJP101.2, PBJP102.1, PBJT69.1, PBJT70.2, PBJT98.2, PBJT99.1, PBJT127.1, PBJT128.2, PBJT536.2, PBJT537.1
C12_R8: PBH217.1, PBH218.1, PBJP103.2, PBJP104.1, PBJT156.1, PBJT157.2, PBJT185.2, PBJT186.1, PBJT538.2, PBJT539.1
C12_R10: PBH219.1, PBH220.1, PBH221.1, PBJP104.2, PBJP105.1, PBJT214.1, PBJT215.2, PBJT243.2, PBJT244.1, PBJT272.1, PBJT273.2, PBJT539.2, PBJT540.1
C12_R14: PBH223.1, PBH224.1, PBJP106.2, PBJP107.1, PBJT301.1, PBJT302.2, PBJT330.2, PBJT331.1, PBJT541.2, PBJT542.1
C12_R16: PBH225.1, PBH226.1, PBH227.1, PBJP107.2, PBJP108.1, PBJT359.1, PBJT360.2, PBJT388.2, PBJT389.1, PBJT417.1, PBJT418.2, PBJT542.2, PBJT543.1
C13_R2: PBH230.1, PBH231.1, PBIS12.1, PBIS13.1, PBJP109.2, PBJP110.1, PBJT12.1, PBJT13.2, PBJT41.2, PBJT42.1, PBJT544.1, PBJT545.2
C13_R4: PBH232.1, PBH233.1, PBH234.1, PBIS40.1, PBIS41.1, PBJP110.2, PBJP111.1, PBJT70.1, PBJT71.2, PBJT99.2, PBJT100.1, PBJT128.1, PBJT129.2, PBJT545.1, PBJT546.2
C13_R8: PBH236.1, PBH237.1, PBIS68.1, PBIS69.1, PBJP112.2, PBJP113.1, PBJT157.1, PBJT158.2, PBJT186.2, PBJT187.1, PBJT547.1, PBJT548.2
C13_R10: PBH238.1, PBH239.1, PBH240.1, PBIS96.1, PBIS97.1, PBJP113.2, PBJP114.1, PBJT215.1, PBJT216.2, PBJT244.2, PBJT245.1, PBJT273.1, PBJT274.2, PBJT548.1, PBJT549.2
C13_R14: PBH242.1, PBH243.1, PBIS124.1, PBIS125.1, PBJP115.2, PBJP116.1, PBJT302.1, PBJT303.2, PBJT331.2, PBJT332.1, PBJT550.1, PBJT551.2
C13_R16: PBH244.1, PBH245.1, PBH246.1, PBIS152.1, PBIS153.1, PBJP116.2, PBJP117.1, PBJT360.1, PBJT361.2, PBJT389.2, PBJT390.1, PBJT418.1, PBJT419.2, PBJT551.1, PBJT552.2
C14_R2: PBH249.1, PBH250.1, PBJP118.2, PBJP119.1, PBJT13.1, PBJT14.2, PBJT42.2, PBJT43.1, PBJT553.2, PBJT554.1
C14_R4: PBH251.1, PBH252.1, PBH253.1, PBJP119.2, PBJP120.1, PBJT71.1, PBJT72.2, PBJT100.2, PBJT101.1, PBJT129.1, PBJT130.2, PBJT554.2, PBJT555.1
C14_R8: PBH255.1, PBH256.1, PBJP121.2, PBJP122.1, PBJT158.1, PBJT159.2, PBJT187.2, PBJT188.1, PBJT556.2, PBJT557.1
C14_R10: PBH257.1, PBH258.1, PBH259.1, PBJP122.2, PBJP123.1, PBJT216.1, PBJT217.2, PBJT245.2, PBJT246.1, PBJT274.1, PBJT275.2, PBJT557.2, PBJT558.1
C14_R14: PBH261.1, PBH262.1, PBJP124.2, PBJP125.1, PBJT303.1, PBJT304.2, PBJT332.2, PBJT333.1, PBJT559.2, PBJT560.1
C14_R16: PBH263.1, PBH264.1, PBH265.1, PBJP125.2, PBJP126.1, PBJT361.1, PBJT362.2, PBJT390.2, PBJT391.1, PBJT419.1, PBJT420.2, PBJT560.2, PBJT561.1
C15_R2: PBH268.1, PBH269.1, PBIS14.1, PBIS15.1, PBJP127.2, PBJP128.1, PBJT14.1, PBJT15.2, PBJT43.2, PBJT44.1, PBJT562.1, PBJT563.2
C15_R4: PBH270.1, PBH271.1, PBH272.1, PBIS42.1, PBIS43.1, PBJP128.2, PBJP129.1, PBJT72.1, PBJT73.2, PBJT101.2, PBJT102.1, PBJT130.1, PBJT131.2, PBJT563.1, PBJT564.2
C15_R8: PBH274.1, PBH275.1, PBIS70.1, PBIS71.1, PBJP130.2, PBJP131.1, PBJT159.1, PBJT160.2, PBJT188.2, PBJT189.1, PBJT565.1, PBJT566.2
C15_R10: PBH276.1, PBH277.1, PBH278.1, PBIS98.1, PBIS99.1, PBJP131.2, PBJP132.1, PBJT217.1, PBJT218.2, PBJT246.2, PBJT247.1, PBJT275.1, PBJT276.2, PBJT566.1, PBJT567.2
C15_R14: PBH280.1, PBH281.1, PBIS126.1, PBIS127.1, PBJP133.2, PBJP134.1, PBJT304.1, PBJT305.2, PBJT333.2, PBJT334.1, PBJT568.1, PBJT569.2
C15_R16: PBH282.1, PBH283.1, PBH284.1, PBIS154.1, PBIS155.1, PBJP134.2, PBJP135.1, PBJT362.1, PBJT363.2, PBJT391.2, PBJT392.1, PBJT420.1, PBJT421.2, PBJT569.1, PBJT570.2
C16_R2: PBH287.1, PBH288.1, PBJP136.2, PBJP137.1, PBJT15.1, PBJT16.2, PBJT44.2, PBJT45.1, PBJT571.2, PBJT572.1
C16_R4: PBH289.1, PBH290.1, PBH291.1, PBJP137.2, PBJP138.1, PBJT73.1, PBJT74.2, PBJT102.2, PBJT103.1, PBJT131.1, PBJT132.2, PBJT572.2, PBJT573.1
C16_R8: PBH293.1, PBH294.1, PBJP139.2, PBJP140.1, PBJT160.1, PBJT161.2, PBJT189.2, PBJT190.1, PBJT574.2, PBJT575.1
C16_R10: PBH295.1, PBH296.1, PBH297.1, PBJP140.2, PBJP141.1, PBJT218.1, PBJT219.2, PBJT247.2, PBJT248.1, PBJT276.1, PBJT277.2, PBJT575.2, PBJT576.1
C16_R14: PBH299.1, PBH300.1, PBJP142.2, PBJP143.1, PBJT305.1, PBJT306.2, PBJT334.2, PBJT335.1, PBJT577.2, PBJT578.1
C16_R16: PBH301.1, PBH302.1, PBH303.1, PBJP143.2, PBJP144.1, PBJT363.1, PBJT364.2, PBJT392.2, PBJT393.1, PBJT421.1, PBJT422.2, PBJT578.2, PBJT579.1
C17_R2: PBH306.1, PBH307.1, PBIS16.1, PBIS17.1, PBJP145.2, PBJP146.1, PBJT16.1, PBJT17.2, PBJT45.2, PBJT46.1, PBJT580.1, PBJT581.2
C17_R4: PBH308.1, PBH309.1, PBH310.1, PBIS44.1, PBIS45.1, PBJP146.2, PBJP147.1, PBJT74.1, PBJT75.2, PBJT103.2, PBJT104.1, PBJT132.1, PBJT133.2, PBJT581.1, PBJT582.2
C17_R8: PBH312.1, PBH313.1, PBIS72.1, PBIS73.1, PBJP148.2, PBJP149.1, PBJT161.1, PBJT162.2, PBJT190.2, PBJT191.1, PBJT583.1, PBJT584.2
C17_R10: PBH314.1, PBH315.1, PBH316.1, PBIS100.1, PBIS101.1, PBJP149.2, PBJP150.1, PBJT219.1, PBJT220.2, PBJT248.2, PBJT249.1, PBJT277.1, PBJT278.2, PBJT584.1, PBJT585.2
C17_R14: PBH318.1, PBH319.1, PBIS128.1, PBIS129.1, PBJP151.2, PBJP152.1, PBJT306.1, PBJT307.2, PBJT335.2, PBJT336.1, PBJT586.1, PBJT587.2
C17_R16: PBH320.1, PBH321.1, PBH322.1, PBIS156.1, PBIS157.1, PBJP152.2, PBJP153.1, PBJT364.1, PBJT365.2, PBJT393.2, PBJT394.1, PBJT422.1, PBJT423.2, PBJT587.1, PBJT588.2
C18_R2: PBH325.1, PBH326.1, PBJP154.2, PBJP155.1, PBJT17.1, PBJT18.2, PBJT46.2, PBJT47.1, PBJT589.2, PBJT590.1
C18_R4: PBH327.1, PBH328.1, PBH329.1, PBJP155.2, PBJP156.1, PBJT75.1, PBJT76.2, PBJT104.2, PBJT105.1, PBJT133.1, PBJT134.2, PBJT590.2, PBJT591.1
C18_R8: PBH331.1, PBH332.1, PBJP157.2, PBJP158.1, PBJT162.1, PBJT163.2, PBJT191.2, PBJT192.1, PBJT592.2, PBJT593.1
C18_R10: PBH333.1, PBH334.1, PBH335.1, PBJP158.2, PBJP159.1, PBJT220.1, PBJT221.2, PBJT249.2, PBJT250.1, PBJT278.1, PBJT279.2, PBJT593.2, PBJT594.1
C18_R14: PBH337.1, PBH338.1, PBJP160.2, PBJP161.1, PBJT307.1, PBJT308.2, PBJT336.2, PBJT337.1, PBJT595.2, PBJT596.1
C18_R16: PBH339.1, PBH340.1, PBH341.1, PBJP161.2, PBJP162.1, PBJT365.1, PBJT366.2, PBJT394.2, PBJT395.1, PBJT423.1, PBJT424.2, PBJT596.2, PBJT597.1
C19_R2: PBH344.1, PBH345.1, PBIS18.1, PBIS19.1, PBJP163.2, PBJP164.1, PBJT18.1, PBJT19.2, PBJT47.2, PBJT48.1, PBJT598.1, PBJT599.2
C19_R4: PBH346.1, PBH347.1, PBH348.1, PBIS46.1, PBIS47.1, PBJP164.2, PBJP165.1, PBJT76.1, PBJT77.2, PBJT105.2, PBJT106.1, PBJT134.1, PBJT135.2, PBJT599.1, PBJT600.2
C19_R8: PBH350.1, PBH351.1, PBIS74.1, PBIS75.1, PBJP166.2, PBJP167.1, PBJT163.1, PBJT164.2, PBJT192.2, PBJT193.1, PBJT601.1, PBJT602.2
C19_R10: PBH352.1, PBH353.1, PBH354.1, PBIS102.1, PBIS103.1, PBJP167.2, PBJP168.1, PBJT221.1, PBJT222.2, PBJT250.2, PBJT251.1, PBJT279.1, PBJT280.2, PBJT602.1, PBJT603.2
C19_R14: PBH356.1, PBH357.1, PBIS130.1, PBIS131.1, PBJP169.2, PBJP170.1, PBJT308.1, PBJT309.2, PBJT337.2, PBJT338.1, PBJT604.1, PBJT605.2
C19_R16: PBH358.1, PBH359.1, PBH360.1, PBIS158.1, PBIS159.1, PBJP170.2, PBJP171.1, PBJT366.1, PBJT367.2, PBJT395.2, PBJT396.1, PBJT424.1, PBJT425.2, PBJT605.1, PBJT606.2
C20_R2: PBH363.1, PBH364.1, PBJP172.2, PBJP173.1, PBJT19.1, PBJT20.2, PBJT48.2, PBJT49.1, PBJT607.2, PBJT608.1
C20_R4: PBH365.1, PBH366.1, PBH367.1, PBJP173.2, PBJP174.1, PBJT77.1, PBJT78.2, PBJT106.2, PBJT107.1, PBJT135.1, PBJT136.2, PBJT608.2, PBJT609.1
C20_R8: PBH369.1, PBH370.1, PBJP175.2, PBJP176.1, PBJT164.1, PBJT165.2, PBJT193.2, PBJT194.1, PBJT610.2, PBJT611.1
C20_R10: PBH371.1, PBH372.1, PBH373.1, PBJP176.2, PBJP177.1, PBJT222.1, PBJT223.2, PBJT251.2, PBJT252.1, PBJT280.1, PBJT281.2, PBJT611.2, PBJT612.1
C20_R14: PBH375.1, PBH376.1, PBJP178.2, PBJP179.1, PBJT309.1, PBJT310.2, PBJT338.2, PBJT339.1, PBJT613.2, PBJT614.1
C20_R16: PBH377.1, PBH378.1, PBH379.1, PBJP179.2, PBJP180.1, PBJT367.1, PBJT368.2, PBJT396.2, PBJT397.1, PBJT425.1, PBJT426.2, PBJT614.2, PBJT615.1
C21_R2: PBH382.1, PBH383.1, PBIS20.1, PBIS21.1, PBJP181.2, PBJP182.1, PBJT20.1, PBJT21.2, PBJT49.2, PBJT50.1, PBJT616.1, PBJT617.2
C21_R4: PBH384.1, PBH385.1, PBH386.1, PBIS48.1, PBIS49.1, PBJP182.2, PBJP183.1, PBJT78.1, PBJT79.2, PBJT107.2, PBJT108.1, PBJT136.1, PBJT137.2, PBJT617.1, PBJT618.2
C21_R8: PBH388.1, PBH389.1, PBIS76.1, PBIS77.1, PBJP184.2, PBJP185.1, PBJT165.1, PBJT166.2, PBJT194.2, PBJT195.1, PBJT619.1, PBJT620.2
C21_R10: PBH390.1, PBH391.1, PBH392.1, PBIS104.1, PBIS105.1, PBJP185.2, PBJP186.1, PBJT223.1, PBJT224.2, PBJT252.2, PBJT253.1, PBJT281.1, PBJT282.2, PBJT620.1, PBJT621.2
C21_R14: PBH394.1, PBH395.1, PBIS132.1, PBIS133.1, PBJP187.2, PBJP188.1, PBJT310.1, PBJT311.2, PBJT339.2, PBJT340.1, PBJT622.1, PBJT623.2
C21_R16: PBH396.1, PBH397.1, PBH398.1, PBIS160.1, PBIS161.1, PBJP188.2, PBJP189.1, PBJT368.1, PBJT369.2, PBJT397.2, PBJT398.1, PBJT426.1, PBJT427.2, PBJT623.1, PBJT624.2
C22_R2: PBH401.1, PBH402.1, PBJP190.2, PBJP191.1, PBJT21.1, PBJT22.2, PBJT50.2, PBJT51.1, PBJT625.2, PBJT626.1
C22_R4: PBH403.1, PBH404.1, PBH405.1, PBJP191.2, PBJP192.1, PBJT79.1, PBJT80.2, PBJT108.2, PBJT109.1, PBJT137.1, PBJT138.2, PBJT626.2, PBJT627.1
C22_R8: PBH407.1, PBH408.1, PBJP193.2, PBJP194.1, PBJT166.1, PBJT167.2, PBJT195.2, PBJT196.1, PBJT628.2, PBJT629.1
C22_R10: PBH409.1, PBH410.1, PBH411.1, PBJP194.2, PBJP195.1, PBJT224.1, PBJT225.2, PBJT253.2, PBJT254.1, PBJT282.1, PBJT283.2, PBJT629.2, PBJT630.1
C22_R14: PBH413.1, PBH414.1, PBJP196.2, PBJP197.1, PBJT311.1, PBJT312.2, PBJT340.2, PBJT341.1, PBJT631.2, PBJT632.1
C22_R16: PBH415.1, PBH416.1, PBH417.1, PBJP197.2, PBJP198.1, PBJT369.1, PBJT370.2, PBJT398.2, PBJT399.1, PBJT427.1, PBJT428.2, PBJT632.2, PBJT633.1
C23_R2: PBH420.1, PBH421.1, PBIS22.1, PBIS23.1, PBJP199.2, PBJP200.1, PBJT22.1, PBJT23.2, PBJT51.2, PBJT52.1, PBJT634.1, PBJT635.2
C23_R4: PBH422.1, PBH423.1, PBH424.1, PBIS50.1, PBIS51.1, PBJP200.2, PBJP201.1, PBJT80.1, PBJT81.2, PBJT109.2, PBJT110.1, PBJT138.1, PBJT139.2, PBJT635.1, PBJT636.2
C23_R8: PBH426.1, PBH427.1, PBIS78.1, PBIS79.1, PBJP202.2, PBJP203.1, PBJT167.1, PBJT168.2, PBJT196.2, PBJT197.1, PBJT637.1, PBJT638.2
C23_R10: PBH428.1, PBH429.1, PBH430.1, PBIS106.1, PBIS107.1, PBJP203.2, PBJP204.1, PBJT225.1, PBJT226.2, PBJT254.2, PBJT255.1, PBJT283.1, PBJT284.2, PBJT638.1, PBJT639.2
C23_R14: PBH432.1, PBH433.1, PBIS134.1, PBIS135.1, PBJP205.2, PBJP206.1, PBJT312.1, PBJT313.2, PBJT341.2, PBJT342.1, PBJT640.1, PBJT641.2
C23_R16: PBH434.1, PBH435.1, PBH436.1, PBIS162.1, PBIS163.1, PBJP206.2, PBJP207.1, PBJT370.1, PBJT371.2, PBJT399.2, PBJT400.1, PBJT428.1, PBJT429.2, PBJT641.1, PBJT642.2
C24_R2: PBH439.1, PBH440.1, PBJP208.2, PBJP209.1, PBJT23.1, PBJT24.2, PBJT52.2, PBJT53.1, PBJT643.2, PBJT644.1
C24_R4: PBH441.1, PBH442.1, PBH443.1, PBJP209.2, PBJP210.1, PBJT81.1, PBJT82.2, PBJT110.2, PBJT111.1, PBJT139.1, PBJT140.2, PBJT644.2, PBJT645.1
C24_R8: PBH445.1, PBH446.1, PBJP211.2, PBJP212.1, PBJT168.1, PBJT169.2, PBJT197.2, PBJT198.1, PBJT646.2, PBJT647.1
C24_R10: PBH447.1, PBH448.1, PBH449.1, PBJP212.2, PBJP213.1, PBJT226.1, PBJT227.2, PBJT255.2, PBJT256.1, PBJT284.1, PBJT285.2, PBJT647.2, PBJT648.1
C24_R14: PBH451.1, PBH452.1, PBJP214.2, PBJP215.1, PBJT313.1, PBJT314.2, PBJT342.2, PBJT343.1, PBJT649.2, PBJT650.1
C24_R16: PBH453.1, PBH454.1, PBH455.1, PBJP215.2, PBJP216.1, PBJT371.1, PBJT372.2, PBJT400.2, PBJT401.1, PBJT429.1, PBJT430.2, PBJT650.2, PBJT651.1
C25_R2: PBH458.1, PBH459.1, PBIS24.1, PBIS25.1, PBJP217.2, PBJP218.1, PBJT24.1, PBJT25.2, PBJT53.2, PBJT54.1, PBJT652.1, PBJT653.2
C25_R4: PBH460.1, PBH461.1, PBH462.1, PBIS52.1, PBIS53.1, PBJP218.2, PBJP219.1, PBJT82.1, PBJT83.2, PBJT111.2, PBJT112.1, PBJT140.1, PBJT141.2, PBJT653.1, PBJT654.2
C25_R8: PBH464.1, PBH465.1, PBIS80.1, PBIS81.1, PBJP220.2, PBJP221.1, PBJT169.1, PBJT170.2, PBJT198.2, PBJT199.1, PBJT655.1, PBJT656.2
C25_R10: PBH466.1, PBH467.1, PBH468.1, PBIS108.1, PBIS109.1, PBJP221.2, PBJP222.1, PBJT227.1, PBJT228.2, PBJT256.2, PBJT257.1, PBJT285.1, PBJT286.2, PBJT656.1, PBJT657.2
C25_R14: PBH470.1, PBH471.1, PBIS136.1, PBIS137.1, PBJP223.2, PBJP224.1, PBJT314.1, PBJT315.2, PBJT343.2, PBJT344.1, PBJT658.1, PBJT659.2
C25_R16: PBH472.1, PBH473.1, PBH474.1, PBIS164.1, PBIS165.1, PBJP224.2, PBJP225.1, PBJT372.1, PBJT373.2, PBJT401.2, PBJT402.1, PBJT430.1, PBJT431.2, PBJT659.1, PBJT660.2
C26_R2: PBH477.1, PBH478.1, PBJP226.2, PBJP227.1, PBJT25.1, PBJT26.2, PBJT54.2, PBJT55.1, PBJT661.2, PBJT662.1
C26_R4: PBH479.1, PBH480.1, PBH481.1, PBJP227.2, PBJP228.1, PBJT83.1, PBJT84.2, PBJT112.2, PBJT113.1, PBJT141.1, PBJT142.2, PBJT662.2, PBJT663.1
C26_R8: PBH483.1, PBH484.1, PBJP229.2, PBJP230.1, PBJT170.1, PBJT171.2, PBJT199.2, PBJT200.1, PBJT664.2, PBJT665.1
C26_R10: PBH485.1, PBH486.1, PBH487.1, PBJP230.2, PBJP231.1, PBJT228.1, PBJT229.2, PBJT257.2, PBJT258.1, PBJT286.1, PBJT287.2, PBJT665.2, PBJT666.1
C26_R14: PBH489.1, PBH490.1, PBJP232.2, PBJP233.1, PBJT315.1, PBJT316.2, PBJT344.2, PBJT345.1, PBJT667.2, PBJT668.1
C26_R16: PBH491.1, PBH492.1, PBH493.1, PBJP233.2, PBJP234.1, PBJT373.1, PBJT374.2, PBJT402.2, PBJT403.1, PBJT431.1, PBJT432.2, PBJT668.2, PBJT669.1
C27_R2: PBH496.1, PBH497.1, PBIS26.1, PBIS27.1, PBJP235.2, PBJP236.1, PBJT26.1, PBJT27.2, PBJT55.2, PBJT56.1, PBJT670.1, PBJT671.2
C27_R4: PBH498.1, PBH499.1, PBH500.1, PBIS54.1, PBIS55.1, PBJP236.2, PBJP237.1, PBJT84.1, PBJT85.2, PBJT113.2, PBJT114.1, PBJT142.1, PBJT143.2, PBJT671.1, PBJT672.2
C27_R8: PBH502.1, PBH503.1, PBIS82.1, PBIS83.1, PBJP238.2, PBJP239.1, PBJT171.1, PBJT172.2, PBJT200.2, PBJT201.1, PBJT673.1, PBJT674.2
C27_R10: PBH504.1, PBH505.1, PBH506.1, PBIS110.1, PBIS111.1, PBJP239.2, PBJP240.1, PBJT229.1, PBJT230.2, PBJT258.2, PBJT259.1, PBJT287.1, PBJT288.2, PBJT674.1, PBJT675.2
C27_R14: PBH508.1, PBH509.1, PBIS138.1, PBIS139.1, PBJP241.2, PBJP242.1, PBJT316.1, PBJT317.2, PBJT345.2, PBJT346.1, PBJT676.1, PBJT677.2
C27_R16: PBH510.1, PBH511.1, PBH512.1, PBIS166.1, PBIS167.1, PBJP242.2, PBJP243.1, PBJT374.1, PBJT375.2, PBJT403.2, PBJT404.1, PBJT432.1, PBJT433.2, PBJT677.1, PBJT678.2
C28_R2: PBH515.1, PBH516.1, PBJP244.2, PBJP245.1, PBJT27.1, PBJT28.2, PBJT56.2, PBJT57.1, PBJT679.2, PBJT680.1
C28_R4: PBH517.1, PBH518.1, PBH519.1, PBJP245.2, PBJP246.1, PBJT85.1, PBJT86.2, PBJT114.2, PBJT115.1, PBJT143.1, PBJT144.2, PBJT680.2, PBJT681.1
C28_R8: PBH521.1, PBH522.1, PBJP247.2, PBJP248.1, PBJT172.1, PBJT173.2, PBJT201.2, PBJT202.1, PBJT682.2, PBJT683.1
C28_R10: PBH523.1, PBH524.1, PBH525.1, PBJP248.2, PBJP249.1, PBJT230.1, PBJT231.2, PBJT259.2, PBJT260.1, PBJT288.1, PBJT289.2, PBJT683.2, PBJT684.1
C28_R14: PBH527.1, PBH528.1, PBJP250.2, PBJP251.1, PBJT317.1, PBJT318.2, PBJT346.2, PBJT347.1, PBJT685.2, PBJT686.1
C28_R16: PBH529.1, PBH530.1, PBH531.1, PBJP251.2, PBJP252.1, PBJT375.1, PBJT376.2, PBJT404.2, PBJT405.1, PBJT433.1, PBJT434.2, PBJT686.2, PBJT687.1
C29_R2: PBH534.1, PBH535.1, PBIS28.1, PBJP253.2, PBJP254.1, PBJT28.1, PBJT29.2, PBJT57.2, PBJT58.1, PBJT688.1, PBJT689.2
C29_R4: PBH536.1, PBH537.1, PBH538.1, PBIS56.1, PBJP254.2, PBJP255.1, PBJT86.1, PBJT87.2, PBJT115.2, PBJT116.1, PBJT144.1, PBJT145.2, PBJT689.1, PBJT690.2
C29_R8: PBH540.1, PBH541.1, PBIS84.1, PBJP256.2, PBJP257.1, PBJT173.1, PBJT174.2, PBJT202.2, PBJT203.1, PBJT691.1, PBJT692.2
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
